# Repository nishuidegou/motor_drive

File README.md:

# motor_drive

机器人机械臂电机驱动项目。

- `sw/` —— 步进电机驱动软件（Nuvoton M2L31 + 2×AS4950，Keil MDK 工程）
- `hw/` —— 硬件（KiCad 原理图 + PCB + BOM）

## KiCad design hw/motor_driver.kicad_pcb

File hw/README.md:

# 电机驱动板硬件 (KiCad)

机械臂电机驱动板。KiCad 9.0 工程。

## 文件
| 文件 | 说明 |
|---|---|
| `motor_driver.kicad_pro` | KiCad 工程 |
| `motor_driver.kicad_sch` | 原理图 |
| `motor_driver.kicad_pcb` | PCB（4 层板） |
| `motor_driver-altium-import.kicad_sym` | 自定义符号库 |
| `motor_driver.pdf` | 原理图 PDF（便于快速查看） |
| `motor_driver.png` | 板卡预览图 |
| `bom/ibom.html` | 交互式 BOM |

## 关键器件
- MCU：Nuvoton **M2L31LGDAE**（Cortex-M23）
- 电机驱动：**2×AS4950** 全桥（A4950/DRV8870 兼容），A/B 两相
- 编码器：**MT6816** 磁编码器（SPI）
- 电源：**ME3116** 降压（VCC_5V）+ LP2992 LDO（VCC_3V3）
- 通讯：CAN（SN65HVD232）+ UART + I2C + SPI

## 备注
- Gerber 生产文件、KiCad 自动备份（motor_driver-backups/）未纳入仓库。

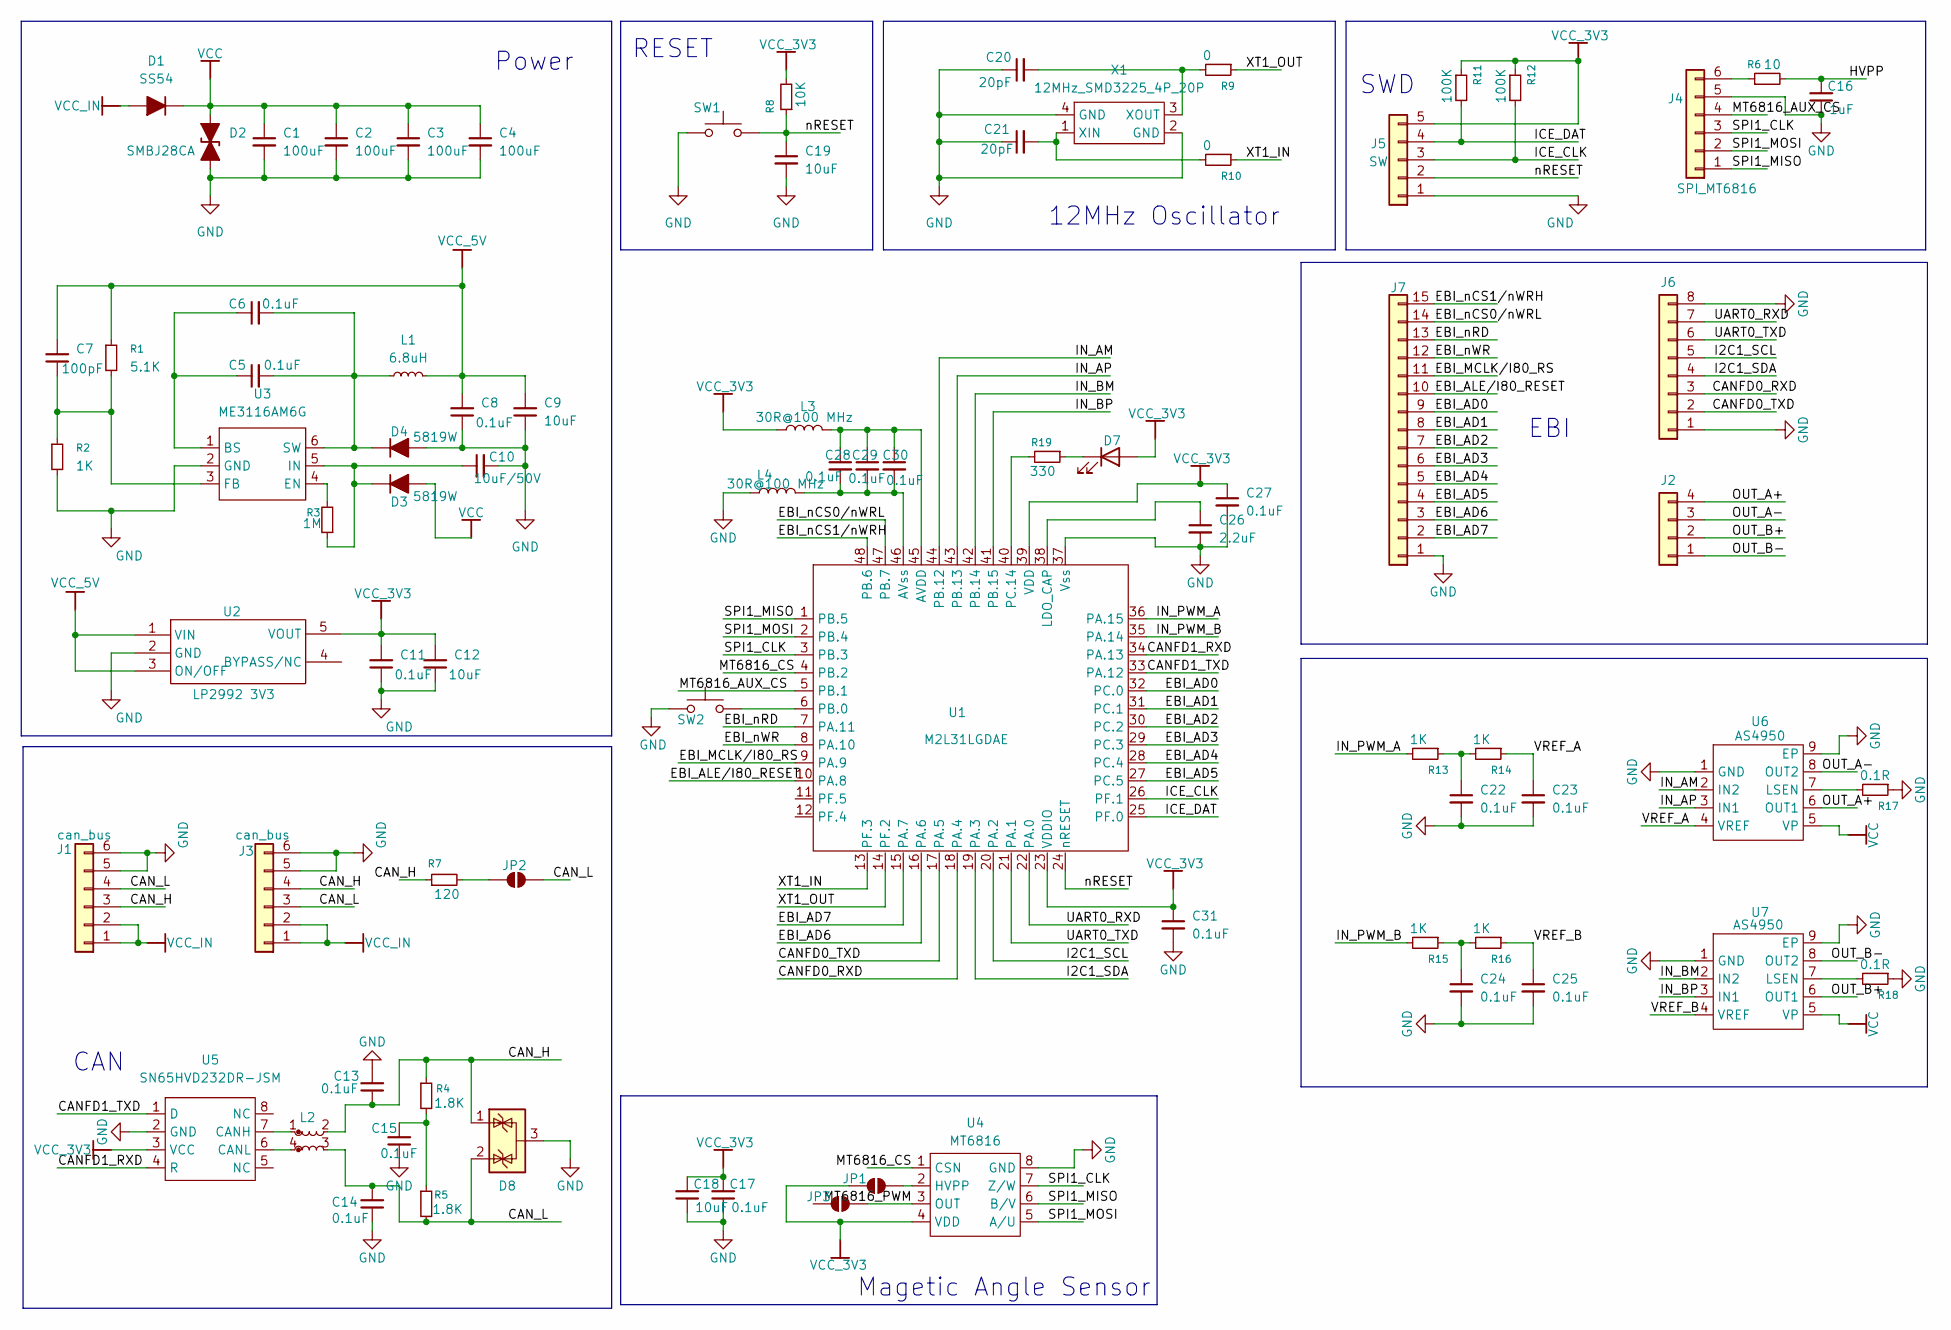
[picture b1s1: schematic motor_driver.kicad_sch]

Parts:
C1, C2, C3, C4: 100uF; 1206-CAP
C5, C6, C8, C11, C13, C14, C15, C17, C22, C23, C24, C25, C27, C28, C29, C30, C31: 0.1uF; CAP_0402
C7: 100pF; CAP_0402
C9, C12, C18, C19: 10uF; CAP_0402
C10: 10uF/50V; CAP_0402
C16: 1uF; CAP_0402
C20, C21: 20pF; CAP_0402
C26: 2.2uF; C_0603_1608Metric
D1: SS54; DO-214AC
D2: SMBJ28CA; SMBJ-CA_MFG
D3, D4: 5819W; SOD-323
D7: 0603_GREEN_19-217/GHC-YR1S2/3T; LED_0603_1608Metric; MPN 19-217/GHC-YR1S2/3T
D8: NUP2105L; SOT-23
J1, J3: can_bus; SH1.0-6P
J2: Conn_01x04; CONN-TH_4P-P2.50_ZX-XH2.54-4PWZ
J4: SPI_MT6816; SH1.0-6P
J5: SW; PinHeader_1x05_P1.27mm_Vertical
J6: Conn_01x08; CONN-SMD_8P-P1.00_MEGASTAR_ZX-SH1.0-8PWT
J7: Conn_01x15; Hirose_FH12-15S-0.5SH_1x15-1MP_P0.50mm_Horizontal
JP1, JP2, JP3: SolderJumper_2_Open; RES_0402
L1: 6.8uH; IND-201612
L2: L_Coupled_Small; L_CommonMode_Wurth_WE-CNSW-1206
L3, L4: FB_2A_0805_220R@100MHz_BLM21PG221SN1D; L_0805_2012Metric_Pad1.15x1.40mm_HandSolder; Rating 2A; MPN BLM21PG221SN1D
R1: 5.1K; RES_0402
R2, R13, R14, R15, R16: 1K; RES_0402
R3: 1M; RES_0402
R4, R5: 1.8K; RES_0402
R6: 10; RES_0402
R7: 120; RES_0402
R8: 10K; RES_0402
R9, R10: 0; RES_0402
R11, R12: 100K; RES_0402
R17, R18: 0.1R; 1206-RES
R19: 330; RES_0402
SW1, SW2: SW_Push; SW-SMD_L3.9-W3.0-P4.45
U1: M2L31LGDAE; LQFP-48
U2: LP2992 3V3; SOT23-5
U3: ME3116AM6G; SOT23-6
U4: MT6816; SO-8
U5: SN65HVD232DR-JSM; SO-8
U6, U7: AS4950; SO-8-PAD
X1: 12MHz_SMD3225_4P_20P; CRYSTAL-SMD_4P-L3.2-W2.5-BL

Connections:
/CANFD0_RXD: J6.3, U1.18 (PA.4)
/CANFD0_TXD: J6.2, U1.17 (PA.5)
/CANFD1_RXD: U1.34 (PA.13), U5.4 (R)
/CANFD1_TXD: U1.33 (PA.12), U5.1 (D)
/CAN_H: C13.1, D8.1 (K), J1.3, J3.4, L2.2, R4.1, R7.1
/CAN_L: C14.2, D8.2 (K), J1.4, J3.3, JP2.2 (B), L2.3, R5.2
/EBI_AD0: J7.9, U1.32 (PC.0)
/EBI_AD1: J7.8, U1.31 (PC.1)
/EBI_AD2: J7.7, U1.30 (PC.2)
/EBI_AD3: J7.6, U1.29 (PC.3)
/EBI_AD4: J7.5, U1.28 (PC.4)
/EBI_AD5: J7.4, U1.27 (PC.5)
/EBI_AD6: J7.3, U1.16 (PA.6)
/EBI_AD7: J7.2, U1.15 (PA.7)
/EBI_ALE/I80_RESET: J7.10, U1.10 (PA.8)
/EBI_MCLK/I80_RS: J7.11, U1.9 (PA.9)
/EBI_nCS0/nWRL: J7.14, U1.47 (PB.7)
/EBI_nCS1/nWRH: J7.15, U1.48 (PB.6)
/EBI_nRD: J7.13, U1.7 (PA.11)
/EBI_nWR: J7.12, U1.8 (PA.10)
/HVPP: C16.2, R6.2
/I2C1_SCL: J6.5, U1.20 (PA.2)
/I2C1_SDA: J6.4, U1.19 (PA.3)
/ICE_CLK: J5.3, R12.2, U1.26 (PF.1)
/ICE_DAT: J5.4, R11.2, U1.25 (PF.0)
/IN_AM: U1.44 (PB.12), U6.2 (IN2)
/IN_AP: U1.43 (PB.13), U6.3 (IN1)
/IN_BM: U1.42 (PB.14), U7.2 (IN2)
/IN_BP: U1.41 (PB.15), U7.3 (IN1)
/IN_PWM_A: R13.2, U1.36 (PA.15)
/IN_PWM_B: R15.2, U1.35 (PA.14)
/MT6816_AUX_CS: J4.4, U1.5 (PB.1)
/MT6816_CS: U1.4 (PB.2), U4.1 (CSN)
/MT6816_PWM: JP3.2 (B), U4.3 (OUT)
/OUT_A+: J2.4, U6.6 (OUT1)
/OUT_A-: J2.3, U6.8 (OUT2)
/OUT_B+: J2.2, U7.6 (OUT1)
/OUT_B-: J2.1, U7.8 (OUT2)
/SPI1_CLK: J4.3, U1.3 (PB.3), U4.7 (Z/W)
/SPI1_MISO: J4.1, U1.1 (PB.5), U4.6 (B/V)
/SPI1_MOSI: J4.2, U1.2 (PB.4), U4.5 (A/U)
/UART0_RXD: J6.7, U1.22 (PA.0)
/UART0_TXD: J6.6, U1.21 (PA.1)
/VREF_A: C23.1, R14.1, U6.4 (VREF)
/VREF_B: C25.1, R16.1, U7.4 (VREF)
/XT1_IN: R10.1, U1.13 (PF.3)
/XT1_OUT: R9.1, U1.14 (PF.2)
/nRESET: C19.1, J5.2, R8.1, SW1.2, U1.24 (nRESET)
GND: C1.2, C2.2, C3.2, C4.2, C8.1, C9.1, C10.2, C11.1, C12.1, C13.2, C14.1, C15.1, C16.1, C17.1, C18.1, C19.2, C20.1, C21.1, C22.2, C23.2, C24.2, C25.2, C26.2, C27.2, C31.2, D2.1 (A1), D4.2 (A), D8.3 (A), J1.5, J1.6, J3.5, J3.6, J4.5, J5.1, J6.1, J6.8, J7.1, L4.1, R2.2, R17.1, R18.1, SW1.1, SW2.1, U1.37 (Vss), U2.2 (GND), U3.2 (GND), U4.8 (GND), U5.2 (GND), U6.1 (GND), U6.9 (EP), U7.1 (GND), U7.9 (EP), X1.2 (GND), X1.4 (GND)
unnamed: C15.2, R4.2, R5.1
unnamed: C22.1, R13.1, R14.2
unnamed: C24.1, R15.1, R16.2
unnamed: C10.1, D3.1 (K), R3.1, U3.5 (IN)
unnamed: C5.2, C6.2, D4.1 (K), L1.1, U3.6 (SW)
unnamed: D7.1 (K), R19.1
unnamed: J4.6, R6.1
unnamed: JP1.2 (B), U4.2 (HVPP)
unnamed: JP2.1 (A), R7.2
unnamed: C28.1, C29.1, C30.1, L3.2, U1.45 (AVDD)
unnamed: C28.2, C29.2, C30.2, L4.2, U1.46 (AVss)
unnamed: C26.1, U1.38 (LDO_CAP)
unnamed: SW2.2, U1.6 (PB.0)
unnamed: R19.2, U1.40 (PC.14)
unnamed: C5.1, C6.1, U3.1 (BS)
unnamed: R3.2, U3.4 (EN)
unnamed: C7.1, R1.2, R2.1, U3.3 (FB)
unnamed: L2.1, U5.7 (CANH)
unnamed: L2.4, U5.6 (CANL)
unnamed: R17.2, U6.7 (LSEN)
unnamed: R18.2, U7.7 (LSEN)
unnamed: C21.2, R10.2, X1.1 (XIN)
unnamed: C20.2, R9.2, X1.3 (XOUT)
VCC: C1.1, C2.1, C3.1, C4.1, D1.1 (K), D2.2 (A2), D3.2 (A), U6.5 (VP), U7.5 (VP)
VCC_3V3: C11.2, C12.2, C17.2, C18.2, C27.1, C31.1, D7.2 (A), J5.5, JP1.1 (A), L3.1, R8.2, R11.1, R12.1, U1.23 (VDDIO), U1.39 (VDD), U2.5 (VOUT), U4.4 (VDD), U5.3 (VCC)
VCC_5V: C7.2, C8.2, C9.2, L1.2, R1.1, U2.1 (VIN), U2.3 (ON/OFF)
VCC_IN: D1.2 (A), J1.1, J1.2, J3.1, J3.2

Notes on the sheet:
Magetic Angle Sensor
SWD
EBI
CAN
Power
12MHz Oscillator
RESET

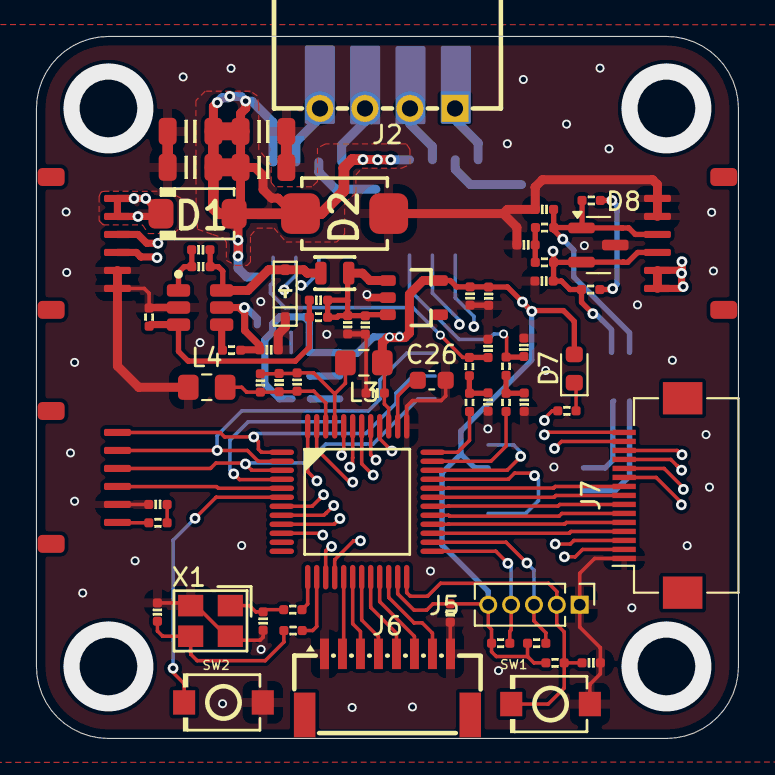
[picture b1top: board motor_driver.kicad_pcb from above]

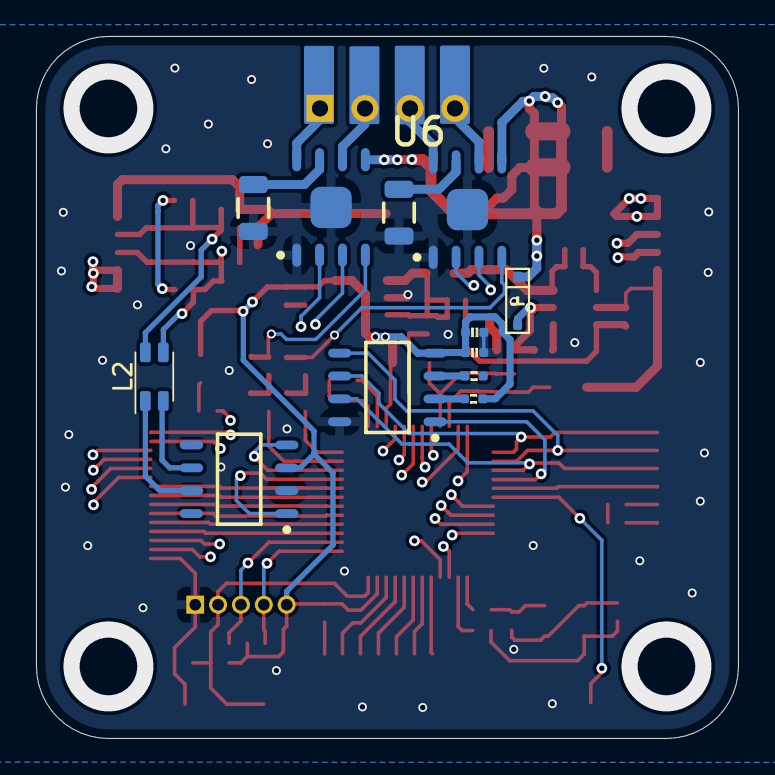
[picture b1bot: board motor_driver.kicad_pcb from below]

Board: 4 copper layers, 39.0 x 39.0 mm, 80 parts (12 on the bottom side), 76 nets.

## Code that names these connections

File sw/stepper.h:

/**************************************************************************//**
 * @file     stepper.h
 * @version  V1.0
 * @brief    两相四线步进电机驱动模块（AS4950 全桥 x2）——接口与配置
 *
 * @note     硬件拓扑（依据 motor_driver.pdf 原理图）：
 *             - 驱动芯片：2 片 AS4950（单全桥，A4950/DRV8870 兼容），
 *               U7 驱动 A 相绕组，U6 驱动 B 相绕组。
 *             - 每个全桥由 IN1/IN2 两个逻辑输入控制方向/刹车/滑行：
 *                 IN1=1,IN2=0 -> OUT1 高、OUT2 低（电流 OUT1 -> OUT2）
 *                 IN1=0,IN2=1 -> OUT1 低、OUT2 高（电流 OUT2 -> OUT1）
 *                 IN1=0,IN2=0 -> 滑行（Coast，桥臂全关，高阻）
 *                 IN1=1,IN2=1 -> 刹车（Brake，两下桥导通）
 *             - VREF 引脚由 MCU 的 PWM 经 RC 低通（1K + 0.1uF）提供，
 *               占空比决定斩波电流门限：I_trip ≈ VREF / (Av * Rsense)。
 *             - MCU 引脚映射：
 *                 PB12 = IN_AM   PB13 = IN_AP   PB14 = IN_BM   PB15 = IN_BP
 *                 PA14 = PWM1_CH4 = VREF_B      PA15 = PWM1_CH5 = VREF_A
 *
 * SPDX-License-Identifier: Apache-2.0
 ****************************************************************************/
#ifndef __STEPPER_H__
#define __STEPPER_H__

#include <stdint.h>
#include "NuMicro.h"

#ifdef __cplusplus
extern "C" {
#endif

/*============================================================================*/
/*  用户配置区（按实际硬件修改）                                              */
/*============================================================================*/

/* ---- 方向控制引脚（AS4950 的 IN1/IN2，均为高电平有效） ---- */
#define STEPPER_PORT        PB          /* 4 个 IN 脚都在 PB 口 */
#define STEPPER_PIN_AP      BIT13       /* PB13 = IN_AP（A 相 IN1） */
#define STEPPER_PIN_AM      BIT12       /* PB12 = IN_AM（A 相 IN2） */
#define STEPPER_PIN_BP      BIT15       /* PB15 = IN_BP（B 相 IN1） */
#define STEPPER_PIN_BM      BIT14       /* PB14 = IN_BM（B 相 IN2） */
#define STEPPER_PIN_ALL     (STEPPER_PIN_AP | STEPPER_PIN_AM | \
                             STEPPER_PIN_BP | STEPPER_PIN_BM)

/* ---- 电流参考 VREF（PWM 输出，经 RC 滤波后进入 AS4950 VREF 脚） ---- */
#define STEPPER_PWM         PWM1
#define STEPPER_VREF_A_CH   5           /* PA15 = PWM1_CH5 = VREF_A */
#define STEPPER_VREF_B_CH   4           /* PA14 = PWM1_CH4 = VREF_B */
#define STEPPER_VREF_CH_MASK  ( (1UL << STEPPER_VREF_A_CH) | (1UL << STEPPER_VREF_B_CH) )

/* ---- 默认参数 ---- */
#define STEPPER_PWM_FREQ            240000UL   /* VREF PWM 频率(Hz)，应 >> RC 截止频率(~1.6kHz) */
#define STEPPER_DEFAULT_CURRENT     50         /* 默认 VREF 占空比(%)，控制相电流大小 */
#define STEPPER_DEFAULT_SPEED_US    1000UL     /* 默认每步周期(us)，1000us = 1ms/步 */

/* ---- 电机参数（1.8° 两相步进电机） ---- */
#define STEPPER_FULL_STEPS_PER_REV  200        /* 整步每转 200 步 */
#define STEPPER_HALF_STEPS_PER_REV  400        /* 半步每转 400 步 */

/*============================================================================*/
/*  类型定义                                                                  */
/*============================================================================*/

/* 步进模式 */
typedef enum {
    STEPPER_MODE_FULL_STEP = 0,     /* 整步：4 拍（2-2 相励磁） */
    STEPPER_MODE_HALF_STEP = 1,     /* 半步：8 拍 */
} stepper_mode_t;

/* 旋转方向 */
typedef enum {
    STEPPER_DIR_CW  = 0,            /* 正向 */
    STEPPER_DIR_CCW = 1,            /* 反向 */
} stepper_dir_t;

/*============================================================================*/
/*  公共接口                                                                  */
/*============================================================================*/

/**
 * @brief  初始化步进电机硬件（GPIO + VREF PWM），并使电机进入断电滑行状态。
 * @note   调用前需已配置系统时钟并调用过 SystemCoreClockUpdate()，
 *         以便内部延时（CLK_SysTickDelay）与 PWM 频率计算正确。
 */
void Stepper_Init(void);

/**
 * @brief  设置步进模式（整步/半步）。
 * @param  mode  见 stepper_mode_t。
 */
void Stepper_SetMode(stepper_mode_t mode);

/**
 * @brief  设置旋转方向。
 * @param  dir  见 stepper_dir_t。
 * @note   若实际转向与预期相反，调用本函数切换方向即可，无需改接线。
 */
void Stepper_SetDirection(stepper_dir_t dir);

/**
 * @brief  设置转速（每步周期）。
 * @param  step_period_us  每步间隔时间（微秒）。数值越小转速越高。
 */
void Stepper_SetSpeed(uint32_t step_period_us);

/**
 * @brief  设置相电流（VREF PWM 占空比）。
 * @param  duty_percent  0~100，对应 VREF 电压 = duty/100 * VDD。
 * @note   占空比越高电流越大。I_trip ≈ (duty/100 * 3.3V) / (Av * Rsense)，
 *         本板 Rsense = 0.1Ω，Av 通常约 10，请按实际数据手册核算。
 */
void Stepper_SetCurrent(uint32_t duty_percent);

/**
 * @brief  按当前方向走一步（非阻塞，调用后立即返回）。
 * @note   步间延时应由调用方控制（配合 Stepper_SetSpeed 的周期自行延时）。
 */
void Stepper_Step(void);

/**
 * @brief  按当前方向连续走 N 步（阻塞）。
 * @param  steps  步数；正数按当前方向走，负数自动反向走 |steps| 步。
 * @note   步间延时使用 Stepper_SetSpeed 设定的周期。
 */
void Stepper_Move(int32_t steps);

/**
 * @brief  停止并断电（滑行 Coast）：四个 IN 全部输出低，桥臂全关。
 */
void Stepper_Stop(void);

/**
 * @brief  刹车（Brake）：四个 IN 全部输出高，两相下桥导通锁轴。
 */
void Stepper_Brake(void);

/**
 * @brief  使能 / 去使能。
 * @param  enable  1 = 按当前相序重新励磁；0 = 断电滑行（同 Stepper_Stop）。
 */
void Stepper_Enable(uint8_t enable);

/**
 * @brief  获取当前位置（相对上电点的累计步数，带符号）。
 * @return 累计步数（整步/半步都按“步”计）。
 */
int32_t Stepper_GetPosition(void);

#ifdef __cplusplus
}
#endif

#endif /* __STEPPER_H__ */
